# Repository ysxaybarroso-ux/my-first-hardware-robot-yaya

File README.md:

# my-first-hardware-robot-yaya
### i'm trying to build my first robot in hardware with 4 paw quite intelligent and that can recive order ! 

# what?
## the different state
  * navigation
  * tracking
  * manual
  * static
### navigation mode
__with this one you will need to use a phone to connect to the  website to the correct ip adress and the the map of the robot lidar will open. All you have to do is chose a point in the phone screen and then... IT WILL GOES TO THE POINT__

### tracking mode
__for the tracking mode you'ill also need a phone or any clickable-device and then the pov of the robot will appear! All you have to do is select the body shape you want to track and then it will follow it__ *educational purpose only*

### manual mode
__again you'ill need your phone or a device, to control the robot with joystick, it can control the motor of the head and the body__ *have fun*

### the static mode 
__what can i say more.... it's static__ *be sure he don't run away TT*

# the cad 
## state
__V1 quite messy will be improved__
not printed don't have any printer for now* 

# specification 
__for the robot i used container in linux with debian and i will use rclp to acces to the NAV2 ODOM and ROS__
__the robot name is nessie and all you have to do to change mode is to  say "nessie mode <mode>"__
*be carefull nessie prefer titanfall2 player to apex one's*
*if you're named anderson or cooper she will love u*

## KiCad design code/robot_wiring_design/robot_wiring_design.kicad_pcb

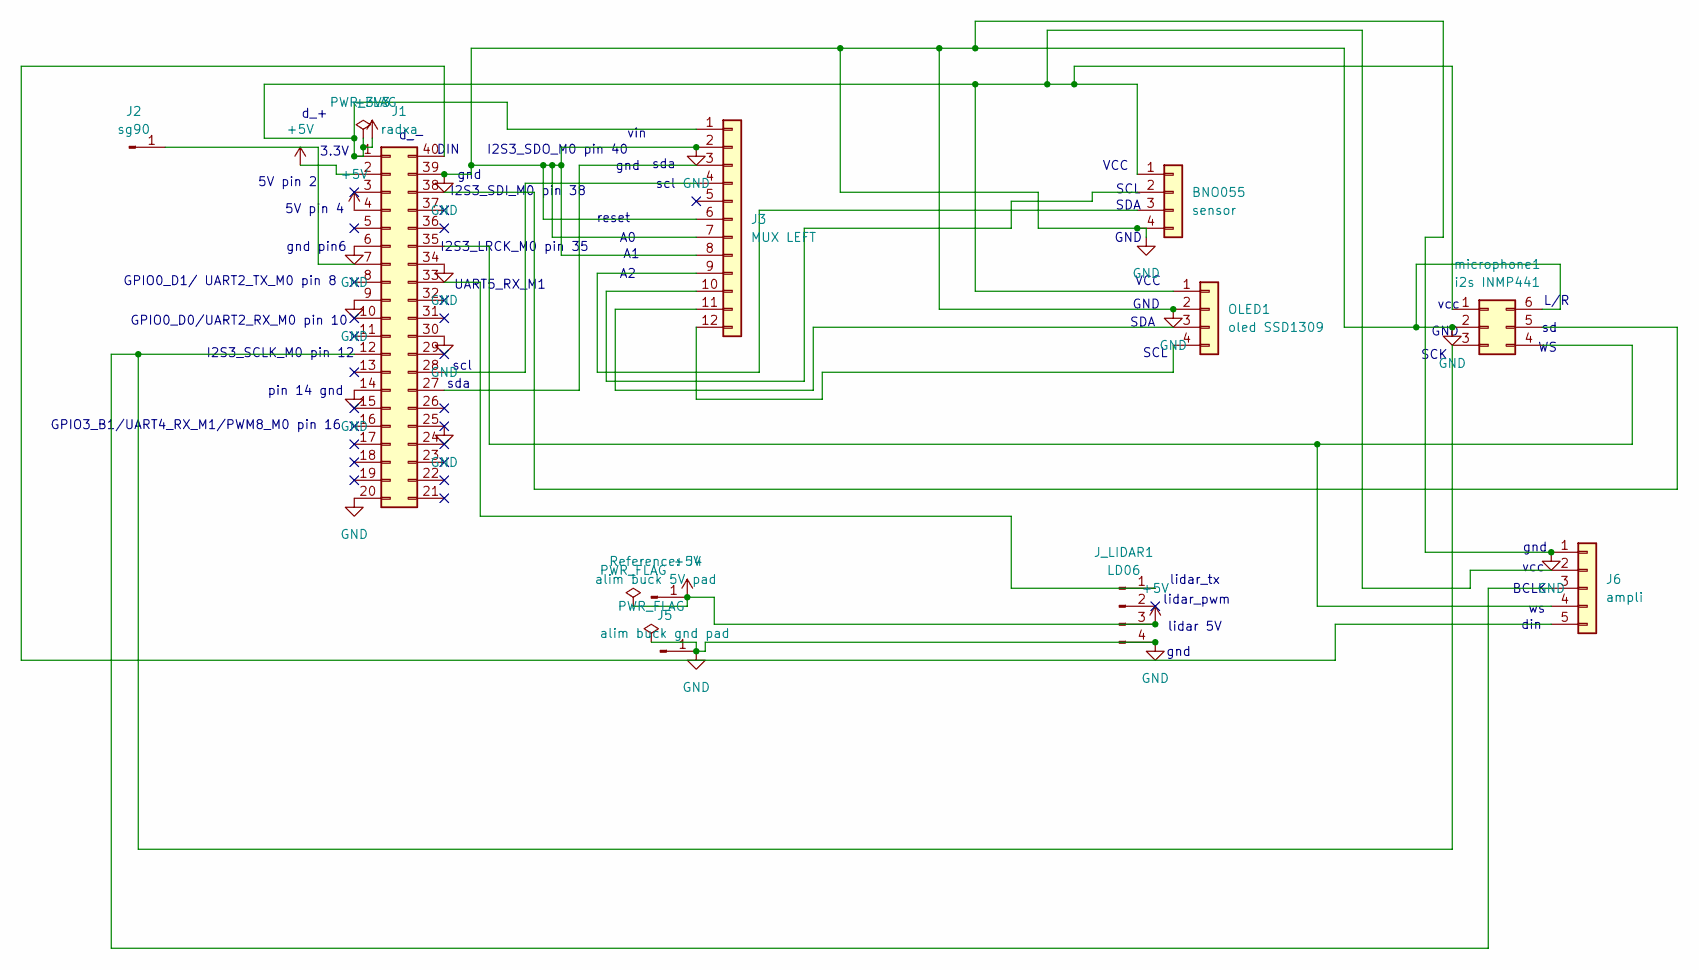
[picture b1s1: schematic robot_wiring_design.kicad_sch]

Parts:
BNO055: sensor; PinHeader_1x04_P2.54mm_Vertical
J1: radxa; PinSocket_2x20_P2.54mm_Vertical
J2: sg90; SolderWirePad_1x01_SMD_5x10mm
J3: MUX LEFT; PinHeader_1x12_P2.54mm_Vertical
J4: alim buck 5V pad; SolderWirePad_1x01_SMD_5x10mm
J5: alim buck gnd pad; SolderWirePad_1x01_SMD_5x10mm
J6: ampli; TerminalBlock_MaiXu_MX126-5.0-05P_1x05_P5.00mm
J_LIDAR1: LD06; TerminalBlock_MaiXu_MX126-5.0-04P_1x04_P5.00mm
OLED1: oled SSD1309; TerminalBlock_MaiXu_MX126-5.0-04P_1x04_P5.00mm
microphone1: i2s INMP441; TerminalBlock_MaiXu_MX126-5.0-06P_1x06_P5.00mm

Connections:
+3V3: BNO055.1, J1.1, J3.1, J6.2, OLED1.1, microphone1.1
+5V: J1.2, J1.4, J4.1 (Pin_1_1), J_LIDAR1.3
GND: BNO055.4, J1.6, J1.9, J1.14, J1.20, J1.25, J1.30, J1.34, J1.39, J3.2, J3.6, J3.7, J3.8, J5.1 (Pin_1_1), J6.1, J_LIDAR1.4, OLED1.2, microphone1.2, microphone1.6
unnamed: BNO055.2, J3.10
unnamed: BNO055.3, J3.9
unnamed: J1.7, J2.1 (Pin_1_1)
unnamed: J1.12, J6.3, microphone1.3
unnamed: J1.27, J3.3
unnamed: J1.28, J3.4
unnamed: J1.33, J_LIDAR1.1
unnamed: J1.35, J6.4, microphone1.4
unnamed: J1.38, microphone1.5
unnamed: J1.40, J6.5
unnamed: J3.11, OLED1.3
unnamed: J3.12, OLED1.4

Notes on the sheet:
d_+
GND
VCC
5V pin 4
gnd
vin
din
vcc
reset
I2S3_LRCK_M0 pin 35
sda
scl
GPIO3_B1/UART4_RX_M1/PWM8_M0 pin 16
SCL
GND
3.3V
I2S3_SCLK_M0 pin 12
I2S3_SDI_M0 pin 38
gnd pin6
gnd
5V pin 2
SCK
SDA
pin 14 gnd
vcc
UART5_RX_M1
DIN I2S3_SDO_M0 pin 40
lidar_pwm
BCLK
lidar 5V
L/R
lidar_tx
GPIO0_D0/UART2_RX_M0 pin 10
GPIO0_D1/ UART2_TX_M0 pin 8
d_-

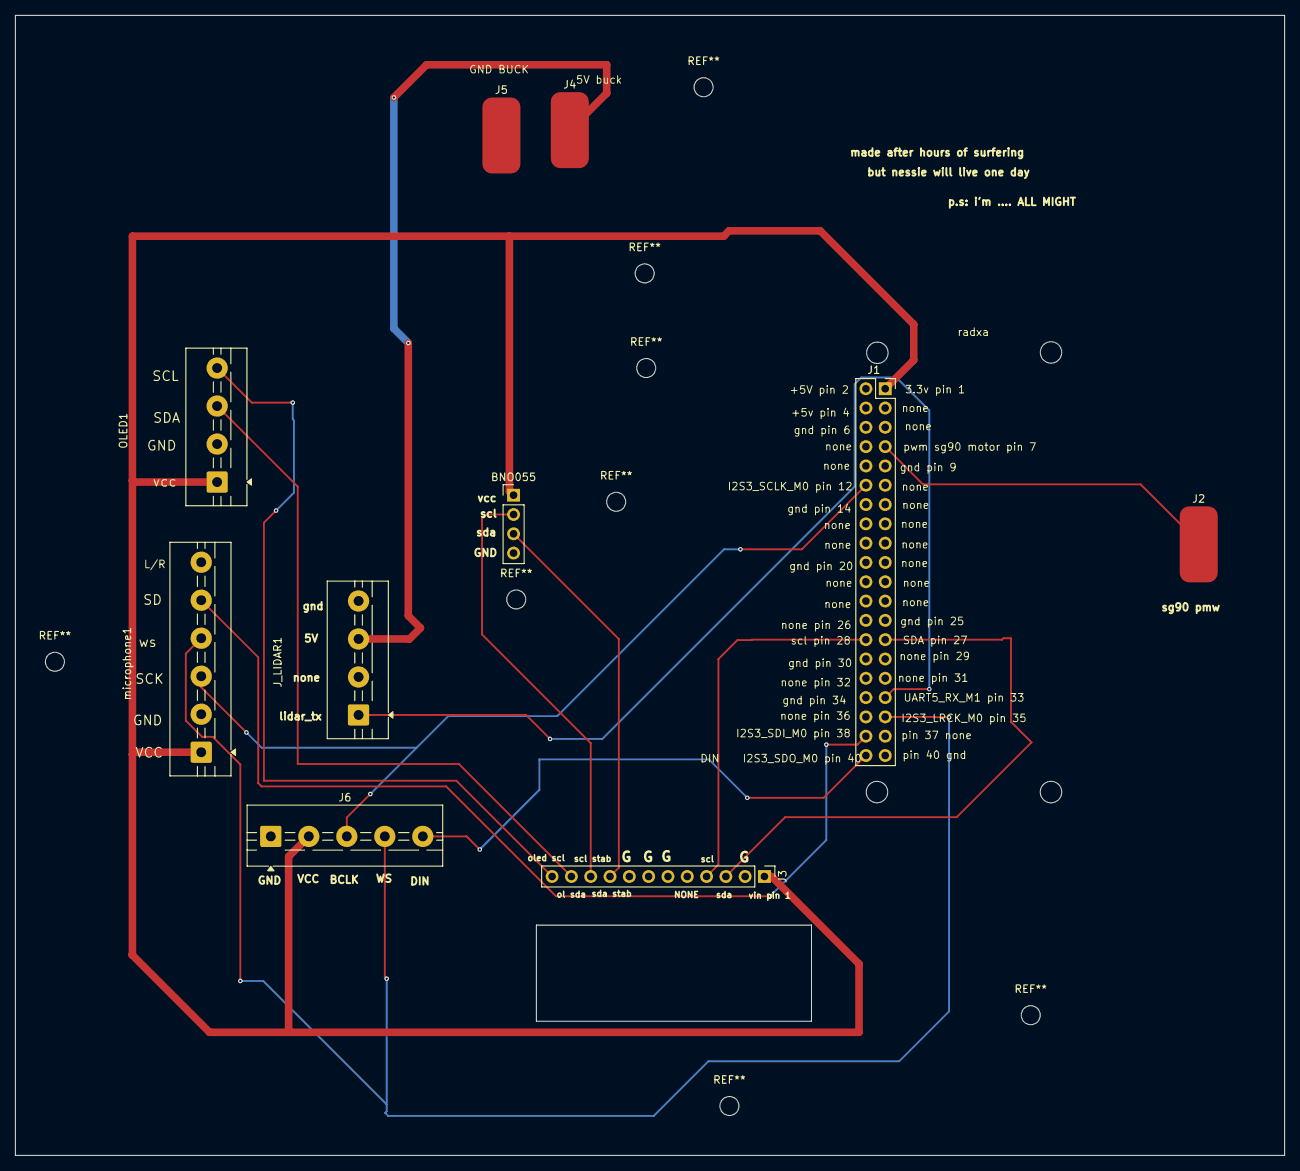
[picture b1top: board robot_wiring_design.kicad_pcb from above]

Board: 2 copper layers, 167.0 x 150.0 mm, 10 parts (0 on the bottom side), 15 nets.
